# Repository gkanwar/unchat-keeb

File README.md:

# Overview
This repository contains the design materials, firmware, and related docs for
two iterations (2023 and 2024) of the **"Unchat" keyboard**.  Highlights of this
design include:

 * An **ergonomic, split form keyboard** with 40 keys (2024) or 42 keys (2023)
 * **Custom Rust firmware** supporting QMK JSON keymaps using a limited feature set
 * **Hardware chatter mitigation** through Hall Effect magnetic switches (2024)
   or hardware debouncing circuitry (2023)
 * **Diode-free** using a 6-bit bus (2023) or 4-bit analog muxes (2024)

Here are some photos.

The **Unchat-42 (2023)**:

Designing the PCB in Kicad and the results:

The **Unchat-40 (2024)** (assembly still WIP):

## Why design a custom keyboard?
This project was motivated in small part by wanting to solve frustrating key
chatter on my main keyboard and in larger part as a way to kill free time during
holiday seasons. It was an awesome way to learn several new skills. I recommend
this sort of project if any of these interest you as well:

 * PCB design in Kicad
 * Mechanical design in OpenSCAD
 * Electronic assembly and debugging
 * Embedded Rust

## Free to use and share
Designs and code in this repository are covered by the CC0 license, allowing
anyone to freely copy, modify, or distribute these materials. Attribution not
required.

That said, there are some known issues with the original designs. These are
documented below, along with my workarounds. In some cases, these issues are
corrected in the latest design files, but corrections have not been tested. You
may discover other issues that I have not personally encountered. **Use at your
own risk!**

# Unchat-40 (2024)

## Design overview
Summary of design features:

 * Two **reversible PCBs** connected via RJ45
 * Controlled by an **Adafruit QT Py RP2040**
 * **Hall-effect** switches queried via **analog muxes**
 * Acrylic and/or aluminum plate and frame

The 2023 design was fairly successful at reducing key chatter without software
debouncing, but I still experienced occasional chatter (see below).
Unfortunately, this was on timescales far above the filtering provided by the
hardware debouncing, likely due to corrosion and mechanical deformation in the
switches due to my terrible assembly process.

With this new 2024 design, I entirely circumvented using electrical contacts by
moving to a Hall Effect magnetic switch design. This is also used in some
"gaming-friendly" keyboards because it allows very rapid triggering, but from
the perspective of this design the main advantage is that we can apply
**hysteresis** to completely eliminate chatter. The cheap DRV5055 sensor
fit the design perfectly. Unfortunately, magnetic switches are still fairly
rare and a bit more pricey, but the overall cost was still manageable.

## Electronic design

## Mechanical design

## Cost breakdown

# Unchat-42 (2023)

More design info and post-mortem coming soon!

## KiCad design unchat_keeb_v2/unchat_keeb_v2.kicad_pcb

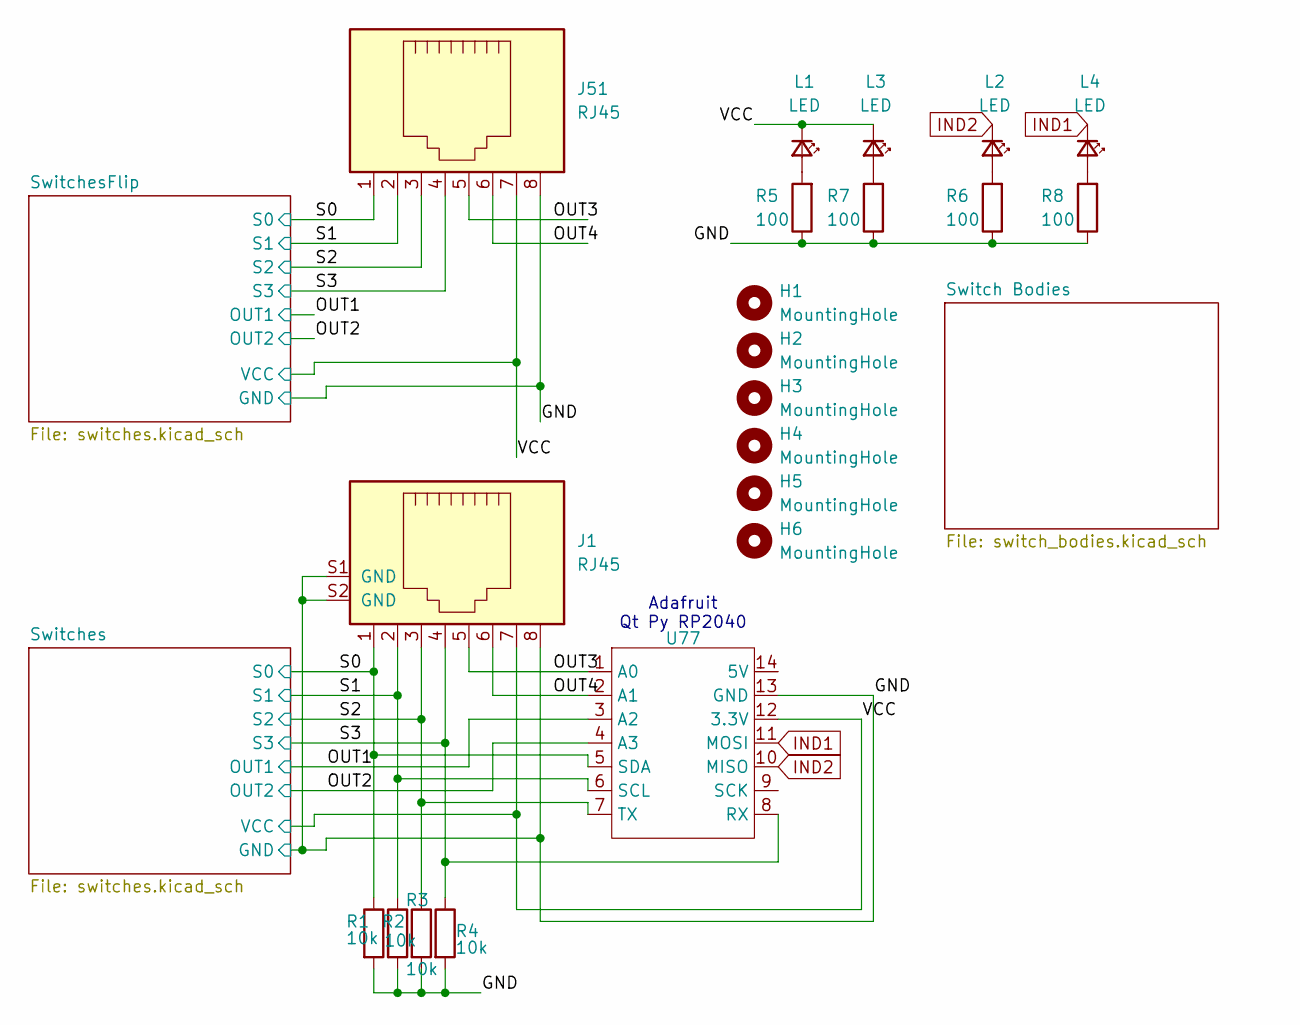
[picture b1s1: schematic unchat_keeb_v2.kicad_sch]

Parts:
H1, H2, H3, H4, H5, H6: MountingHole; MountingHole_2.2mm_M2
J1: RJ45; TE_2041126-1_RJ45
J51: RJ45; TE_2041126-1_RJ45_Back
L1, L2, L3, L4: LED; LED_0603_1608Metric
R1, R2, R3, R4: 10k; R_0805_2012Metric_Pad1.20x1.40mm_HandSolder
R5, R6, R7, R8: 100; R_0805_2012Metric
U77: Adafruit_QT_Py_SMD

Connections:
/GND: J1.8, J1.S1 (GND), J1.S2 (GND), J51.8, R1.2, R2.2, R3.2, R4.2, R5.1, R6.1, R7.1, R8.1, U77.13 (GND); also elsewhere on the board
/OUT1: U77.3 (A2); also elsewhere on the board
/OUT2: U77.4 (A3); also elsewhere on the board
/OUT3: J1.5, J51.5, U77.1 (A0)
/OUT4: J1.6, J51.6, U77.2 (A1)
/S0: J1.1, J51.1, R1.1, U77.5 (SDA); also elsewhere on the board
/S1: J1.2, J51.2, R2.1, U77.6 (SCL); also elsewhere on the board
/S2: J1.3, J51.3, R3.1, U77.7 (TX); also elsewhere on the board
/S3: J1.4, J51.4, R4.1, U77.8 (RX); also elsewhere on the board
/VCC: J1.7, J51.7, L1.1 (K), L3.1 (K), U77.12 (3.3V); also elsewhere on the board
IND1: L4.1 (K), U77.11 (MOSI)
IND2: L2.1 (K), U77.10 (MISO)
unnamed: L1.2 (A), R5.2
unnamed: L2.2 (A), R6.2
unnamed: L3.2 (A), R7.2
unnamed: L4.2 (A), R8.2

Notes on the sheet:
Adafruit Qt Py RP2040

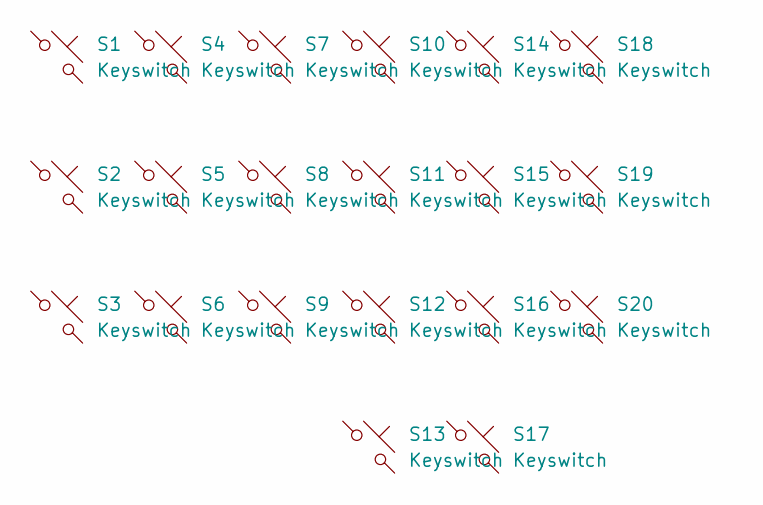
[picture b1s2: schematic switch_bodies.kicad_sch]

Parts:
S1, S2, S3, S4, S5, S6, S7, S8, S9, S10, S11, S12, S13, S14, S15, S16, S17, S18, S19, S20: Keyswitch; MX_HallEffect_Reversible_1.00u

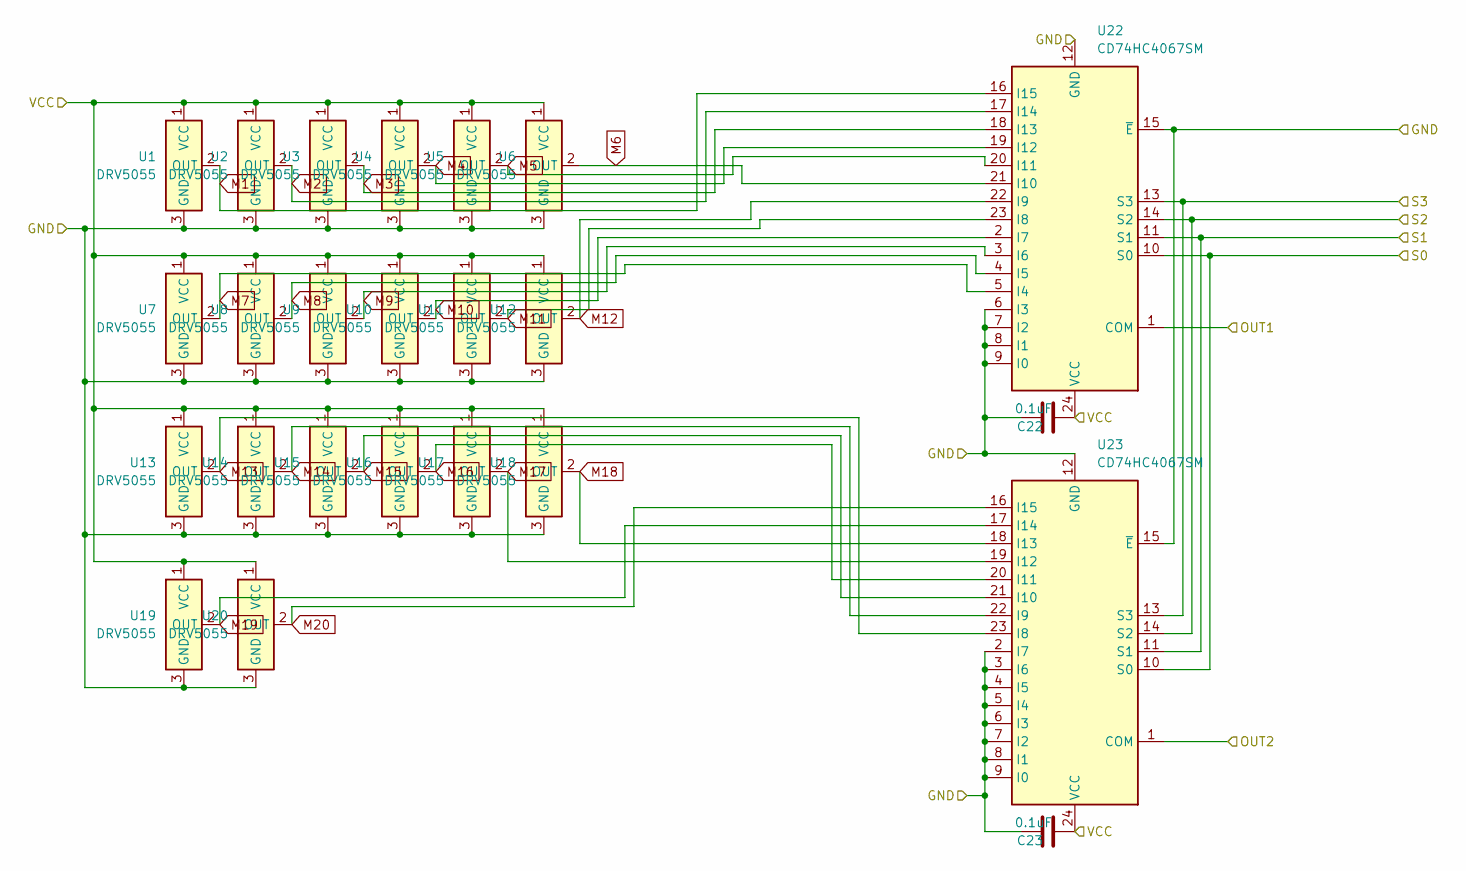
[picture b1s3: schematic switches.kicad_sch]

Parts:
C22, C23: 0.1uF; C_0805_2012Metric_Pad1.18x1.45mm_HandSolder
U1, U2, U3, U4, U5, U6, U7, U8, U9, U10, U11, U12, U13, U14, U15, U16, U17, U18, U19, U20: DRV5055; SOT-23
U22, U23: CD74HC4067SM; SSOP-24_5.3x8.2mm_P0.65mm

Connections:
/GND: C22.1, C23.1, U1.3 (GND), U2.3 (GND), U3.3 (GND), U4.3 (GND), U5.3 (GND), U6.3 (GND), U7.3 (GND), U8.3 (GND), U9.3 (GND), U10.3 (GND), U11.3 (GND), U12.3 (GND), U13.3 (GND), U14.3 (GND), U15.3 (GND), U16.3 (GND), U17.3 (GND), U18.3 (GND), U19.3 (GND), U20.3 (GND), U22.6 (I3), U22.7 (I2), U22.8 (I1), U22.9 (I0), U22.12 (GND), U22.15 (~E), U23.2 (I7), U23.3 (I6), U23.4 (I5), U23.5 (I4), U23.6 (I3), U23.7 (I2), U23.8 (I1), U23.9 (I0), U23.12 (GND), U23.15 (~E); also elsewhere on the board
/OUT1: U22.1 (COM); also elsewhere on the board
/OUT2: U23.1 (COM); also elsewhere on the board
/S0: U22.10 (S0), U23.10 (S0); also elsewhere on the board
/S1: U22.11 (S1), U23.11 (S1); also elsewhere on the board
/S2: U22.14 (S2), U23.14 (S2); also elsewhere on the board
/S3: U22.13 (S3), U23.13 (S3); also elsewhere on the board
/VCC: C22.2, C23.2, U1.1 (VCC), U2.1 (VCC), U3.1 (VCC), U4.1 (VCC), U5.1 (VCC), U6.1 (VCC), U7.1 (VCC), U8.1 (VCC), U9.1 (VCC), U10.1 (VCC), U11.1 (VCC), U12.1 (VCC), U13.1 (VCC), U14.1 (VCC), U15.1 (VCC), U16.1 (VCC), U17.1 (VCC), U18.1 (VCC), U19.1 (VCC), U20.1 (VCC), U22.24 (VCC), U23.24 (VCC); also elsewhere on the board
M1: U1.2 (OUT), U22.16 (I15); also elsewhere on the board
M2: U2.2 (OUT), U22.17 (I14); also elsewhere on the board
M3: U3.2 (OUT), U22.18 (I13); also elsewhere on the board
M4: U4.2 (OUT), U22.19 (I12); also elsewhere on the board
M5: U5.2 (OUT), U22.20 (I11); also elsewhere on the board
M6: U6.2 (OUT), U22.21 (I10); also elsewhere on the board
M7: U7.2 (OUT), U22.5 (I4); also elsewhere on the board
M8: U8.2 (OUT), U22.4 (I5); also elsewhere on the board
M9: U9.2 (OUT), U22.3 (I6); also elsewhere on the board
M10: U10.2 (OUT), U22.2 (I7); also elsewhere on the board
M11: U11.2 (OUT), U22.23 (I8); also elsewhere on the board
M12: U12.2 (OUT), U22.22 (I9); also elsewhere on the board
M13: U13.2 (OUT), U23.23 (I8); also elsewhere on the board
M14: U14.2 (OUT), U23.22 (I9); also elsewhere on the board
M15: U15.2 (OUT), U23.21 (I10); also elsewhere on the board
M16: U16.2 (OUT), U23.20 (I11); also elsewhere on the board
M17: U17.2 (OUT), U23.19 (I12); also elsewhere on the board
M18: U18.2 (OUT), U23.18 (I13); also elsewhere on the board
M19: U19.2 (OUT), U23.17 (I14); also elsewhere on the board
M20: U20.2 (OUT), U23.16 (I15); also elsewhere on the board

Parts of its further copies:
C72, C73: 0.1uF; C_0805_2012Metric_Pad1.18x1.45mm_HandSolder
U51, U52, U53, U54, U55, U56, U57, U58, U59, U60, U61, U62, U63, U64, U65, U66, U67, U68, U69, U70: DRV5055; SOT-23
U72, U73: CD74HC4067SM; SSOP-24_5.3x8.2mm_P0.65mm

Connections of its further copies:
/GND: C72.1, C73.1, U51.3 (GND), U52.3 (GND), U53.3 (GND), U54.3 (GND), U55.3 (GND), U56.3 (GND), U57.3 (GND), U58.3 (GND), U59.3 (GND), U60.3 (GND), U61.3 (GND), U62.3 (GND), U63.3 (GND), U64.3 (GND), U65.3 (GND), U66.3 (GND), U67.3 (GND), U68.3 (GND), U69.3 (GND), U70.3 (GND), U72.6 (I3), U72.7 (I2), U72.8 (I1), U72.9 (I0), U72.12 (GND), U72.15 (~E), U73.2 (I7), U73.3 (I6), U73.4 (I5), U73.5 (I4), U73.6 (I3), U73.7 (I2), U73.8 (I1), U73.9 (I0), U73.12 (GND), U73.15 (~E); also elsewhere on the board
/OUT1: U72.1 (COM); also elsewhere on the board
/OUT2: U73.1 (COM); also elsewhere on the board
/S0: U72.10 (S0), U73.10 (S0); also elsewhere on the board
/S1: U72.11 (S1), U73.11 (S1); also elsewhere on the board
/S2: U72.14 (S2), U73.14 (S2); also elsewhere on the board
/S3: U72.13 (S3), U73.13 (S3); also elsewhere on the board
/VCC: C72.2, C73.2, U51.1 (VCC), U52.1 (VCC), U53.1 (VCC), U54.1 (VCC), U55.1 (VCC), U56.1 (VCC), U57.1 (VCC), U58.1 (VCC), U59.1 (VCC), U60.1 (VCC), U61.1 (VCC), U62.1 (VCC), U63.1 (VCC), U64.1 (VCC), U65.1 (VCC), U66.1 (VCC), U67.1 (VCC), U68.1 (VCC), U69.1 (VCC), U70.1 (VCC), U72.24 (VCC), U73.24 (VCC); also elsewhere on the board
M1: U51.2 (OUT), U72.16 (I15); also elsewhere on the board
M2: U52.2 (OUT), U72.17 (I14); also elsewhere on the board
M3: U53.2 (OUT), U72.18 (I13); also elsewhere on the board
M4: U54.2 (OUT), U72.19 (I12); also elsewhere on the board
M5: U55.2 (OUT), U72.20 (I11); also elsewhere on the board
M6: U56.2 (OUT), U72.21 (I10); also elsewhere on the board
M7: U57.2 (OUT), U72.5 (I4); also elsewhere on the board
M8: U58.2 (OUT), U72.4 (I5); also elsewhere on the board
M9: U59.2 (OUT), U72.3 (I6); also elsewhere on the board
M10: U60.2 (OUT), U72.2 (I7); also elsewhere on the board
M11: U61.2 (OUT), U72.23 (I8); also elsewhere on the board
M12: U62.2 (OUT), U72.22 (I9); also elsewhere on the board
M13: U63.2 (OUT), U73.23 (I8); also elsewhere on the board
M14: U64.2 (OUT), U73.22 (I9); also elsewhere on the board
M15: U65.2 (OUT), U73.21 (I10); also elsewhere on the board
M16: U66.2 (OUT), U73.20 (I11); also elsewhere on the board
M17: U67.2 (OUT), U73.19 (I12); also elsewhere on the board
M18: U68.2 (OUT), U73.18 (I13); also elsewhere on the board
M19: U69.2 (OUT), U73.17 (I14); also elsewhere on the board
M20: U70.2 (OUT), U73.16 (I15); also elsewhere on the board

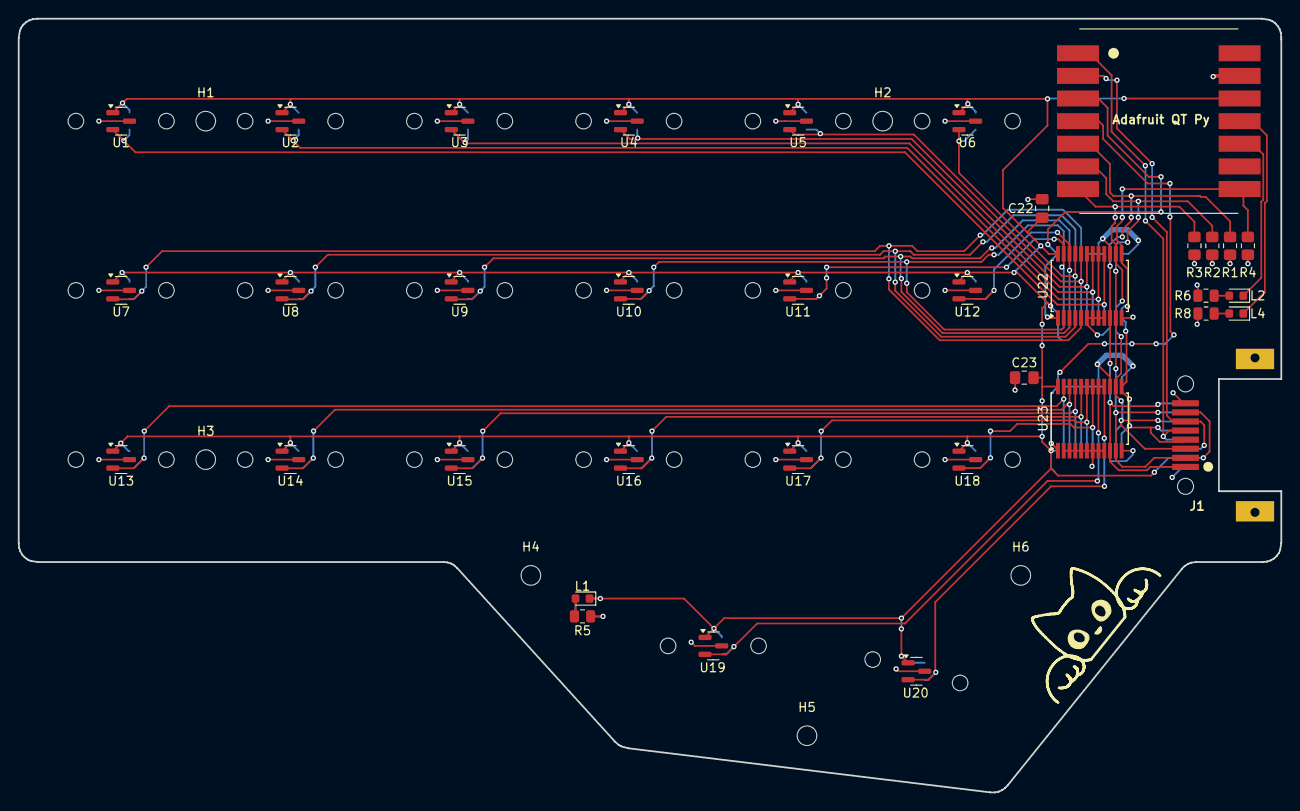
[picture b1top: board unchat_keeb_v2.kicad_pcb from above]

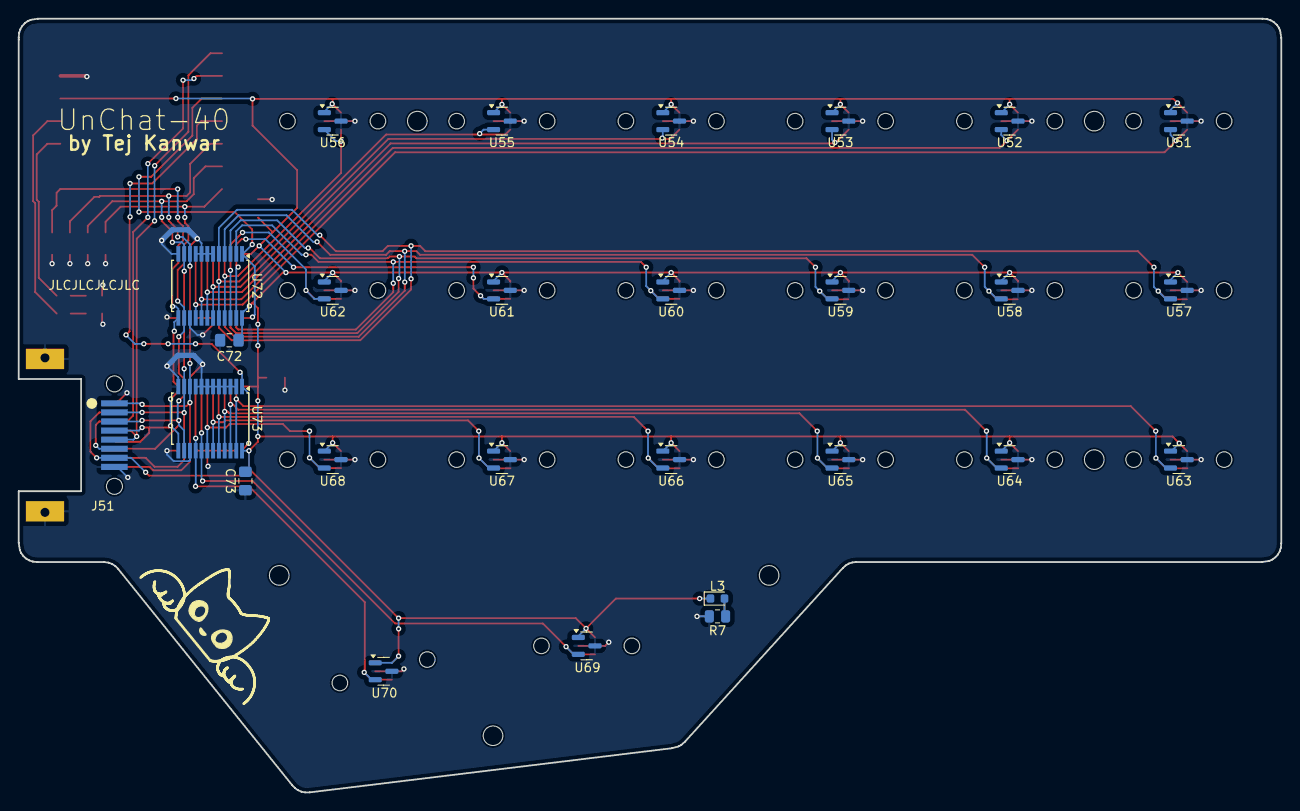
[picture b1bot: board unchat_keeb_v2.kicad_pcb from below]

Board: 2 copper layers, 141.8 x 86.9 mm, 89 parts (27 on the bottom side), 36 nets.

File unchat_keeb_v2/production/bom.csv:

Designator,Footprint,Quantity,Value,LCSC Part #
"C22, C23, C72, C73",0805,4,0.1uF,
J1,TE_2041126-1_RJ45,1,RJ45,
J51,TE_2041126-1_RJ45_Back,1,RJ45,
"L1, L2, L3, L4",0603,4,LED,
"R1, R2, R3, R4",0805,4,10k,
"R5, R6, R7, R8",0805,4,100,
"S1, S10, S11, S12, S13, S14, S15, S16, S17, S18, S19, S2, S20, S3, S4, S5, S6, S7, S8, S9",MX_HallEffect_Reversible_1.00u,20,Keyswitch,
"U1, U10, U11, U12, U13, U14, U15, U16, U17, U18, U19, U2, U20, U3, U4, U5, U51, U52, U53, U54, U55, U56, U57, U58, U59, U6, U60, U61, U62, U63, U64, U65, U66, U67, U68, U69, U7, U70, U8, U9",SOT-23,40,DRV5055,
"U22, U23, U72, U73",SSOP-24_5.3x8.2mm_P0.65mm,4,CD74HC4067SM,
U77,Adafruit_QT_Py_SMD,1,~,

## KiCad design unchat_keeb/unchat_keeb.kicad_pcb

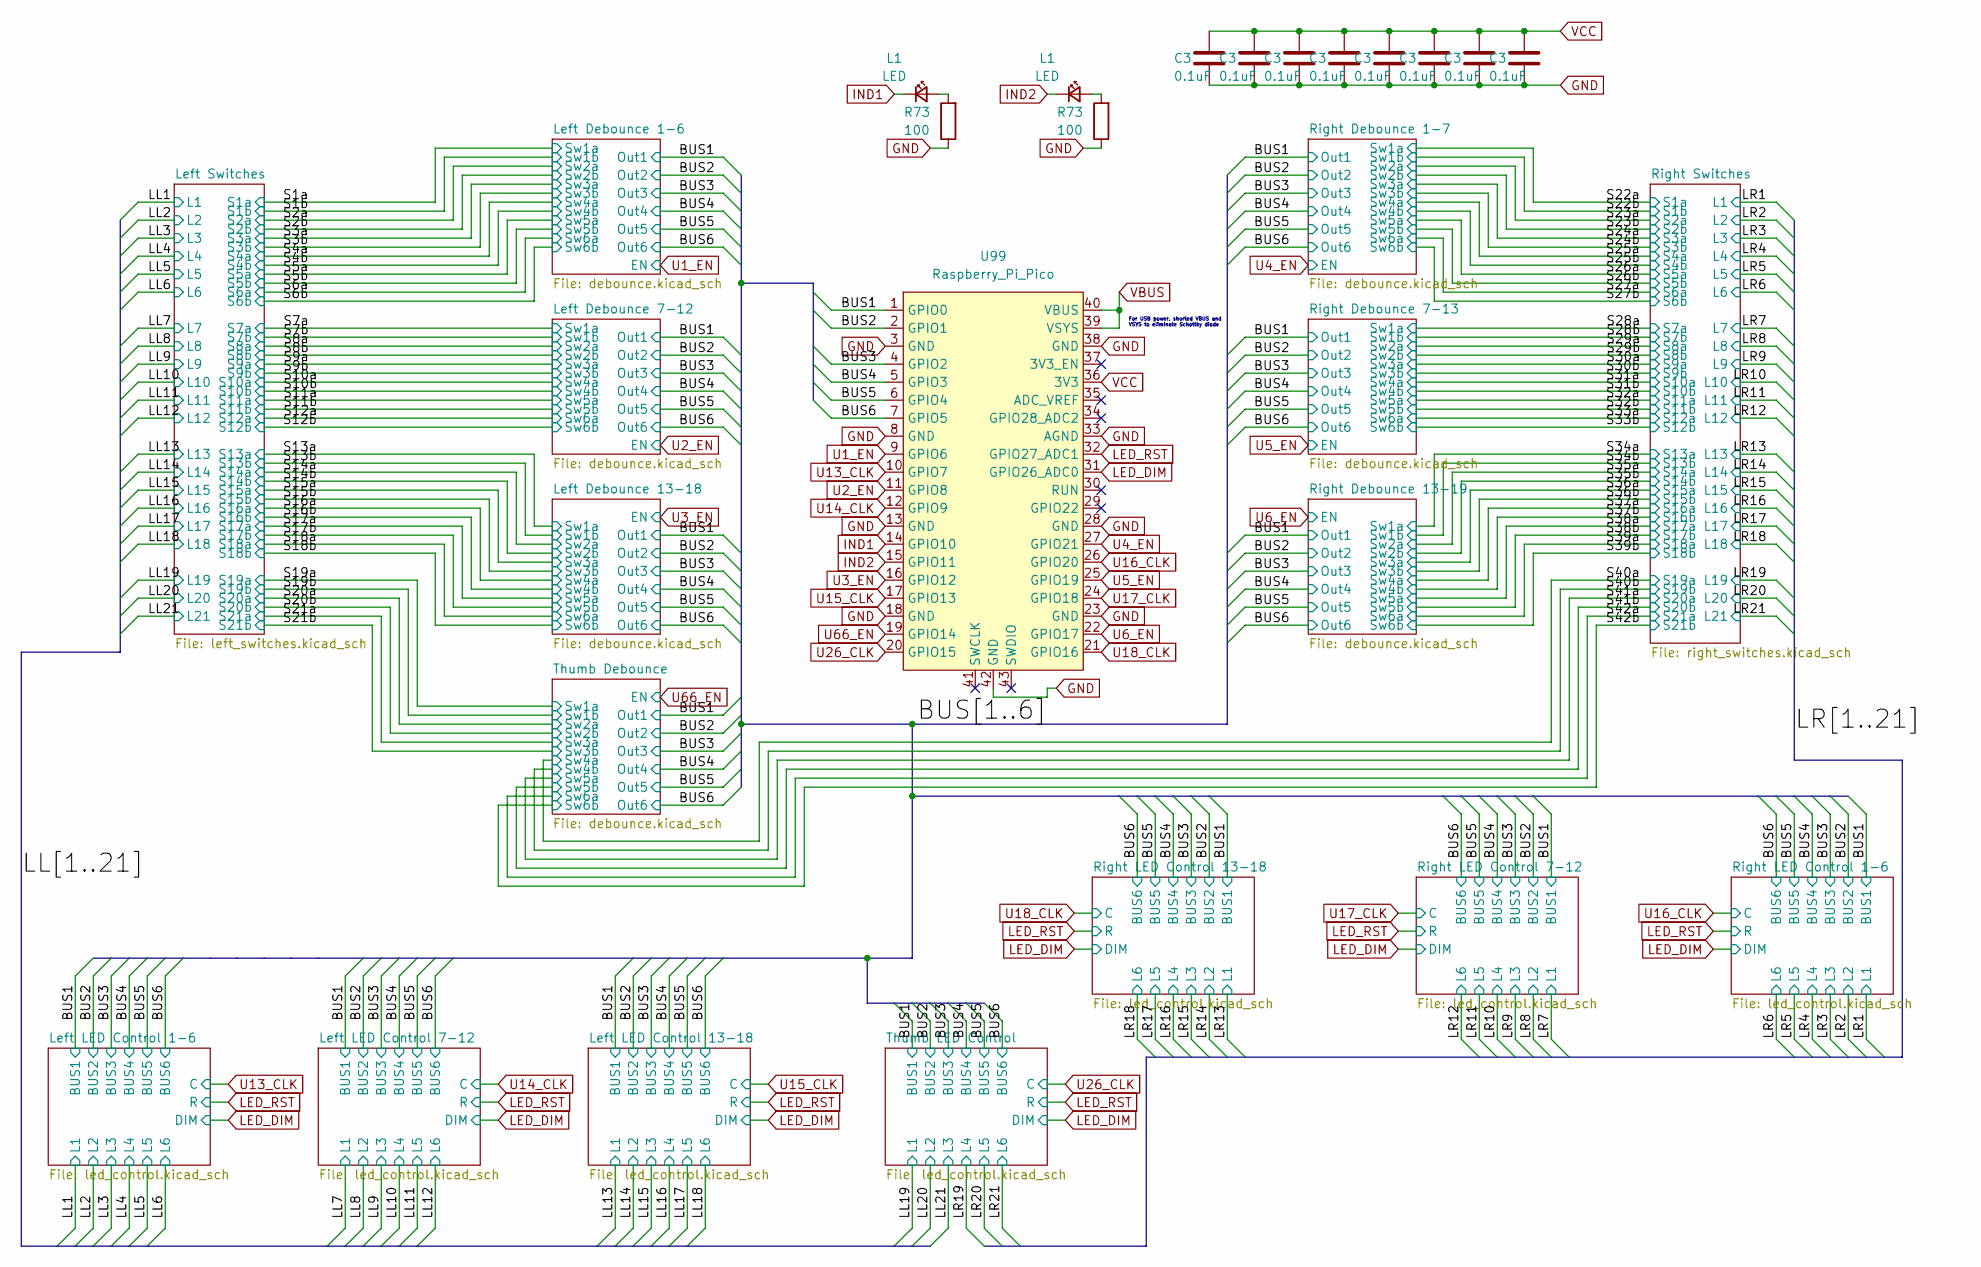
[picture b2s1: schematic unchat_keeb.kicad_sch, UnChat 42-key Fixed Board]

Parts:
C3: 0.1uF; C_0805_2012Metric
L1: LED; LED_0603_1608Metric
R73: 100; R_0805_2012Metric
U99: Raspberry_Pi_Pico; Raspberry_Pi_Pico_SMD

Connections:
/BUS1: U99.1 (GPIO0); also elsewhere on the board
/BUS2: U99.2 (GPIO1); also elsewhere on the board
/BUS3: U99.4 (GPIO2); also elsewhere on the board
/BUS4: U99.5 (GPIO3); also elsewhere on the board
/BUS5: U99.6 (GPIO4); also elsewhere on the board
/BUS6: U99.7 (GPIO5); also elsewhere on the board
GND: C3.2, R73.1, U99.3 (GND), U99.8 (GND), U99.13 (GND), U99.18 (GND), U99.23 (GND), U99.28 (GND), U99.33 (AGND), U99.38 (GND), U99.42 (GND); also elsewhere on the board
LED_DIM: U99.31 (GPIO26_ADC0); also elsewhere on the board
LED_RST: U99.32 (GPIO27_ADC1); also elsewhere on the board
unnamed: L1.2 (A), R73.2
U1_EN: U99.9 (GPIO6); also elsewhere on the board
U2_EN: U99.11 (GPIO8); also elsewhere on the board
U3_EN: U99.16 (GPIO12); also elsewhere on the board
U4_EN: U99.27 (GPIO21); also elsewhere on the board
U5_EN: U99.25 (GPIO19); also elsewhere on the board
U6_EN: U99.22 (GPIO17); also elsewhere on the board
U13_CLK: U99.10 (GPIO7); also elsewhere on the board
U14_CLK: U99.12 (GPIO9); also elsewhere on the board
U15_CLK: U99.17 (GPIO13); also elsewhere on the board
U16_CLK: U99.26 (GPIO20); also elsewhere on the board
U17_CLK: U99.24 (GPIO18); also elsewhere on the board
U18_CLK: U99.21 (GPIO16); also elsewhere on the board
U26_CLK: U99.20 (GPIO15); also elsewhere on the board
U66_EN: U99.19 (GPIO14); also elsewhere on the board
VBUS: U99.39 (VSYS), U99.40 (VBUS)

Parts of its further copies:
C9, C15, C21, C27, C33, C39, C43, C44, C45, C46, C47, C48, C49, C50: 0.1uF; C_0805_2012Metric
L37, L38: LED; LED_0603_1608Metric
R109, R110: 100; R_0805_2012Metric

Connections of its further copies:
/Left Debounce 7-12/Db3: C9.1; also elsewhere on the board
/Left Debounce 13-18/Db3: C15.1; also elsewhere on the board
/Right Debounce 1-7/Db3: C21.1; also elsewhere on the board
/Right Debounce 7-13/Db3: C27.1; also elsewhere on the board
/Right Debounce 13-19/Db3: C33.1; also elsewhere on the board
/Thumb Debounce/Db3: C39.1; also elsewhere on the board
GND: C9.2, C15.2, C21.2, C27.2, C33.2, C39.2, C43.2, C44.2, C45.2, C46.2, C47.2, C48.2, C49.2, C50.2, R109.1, R110.1; also elsewhere on the board
unnamed: L37.2 (A), R109.2
unnamed: L38.2 (A), R110.2

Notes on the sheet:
For USB power, shorted VBUS and VSYS to eliminate Schottky diode

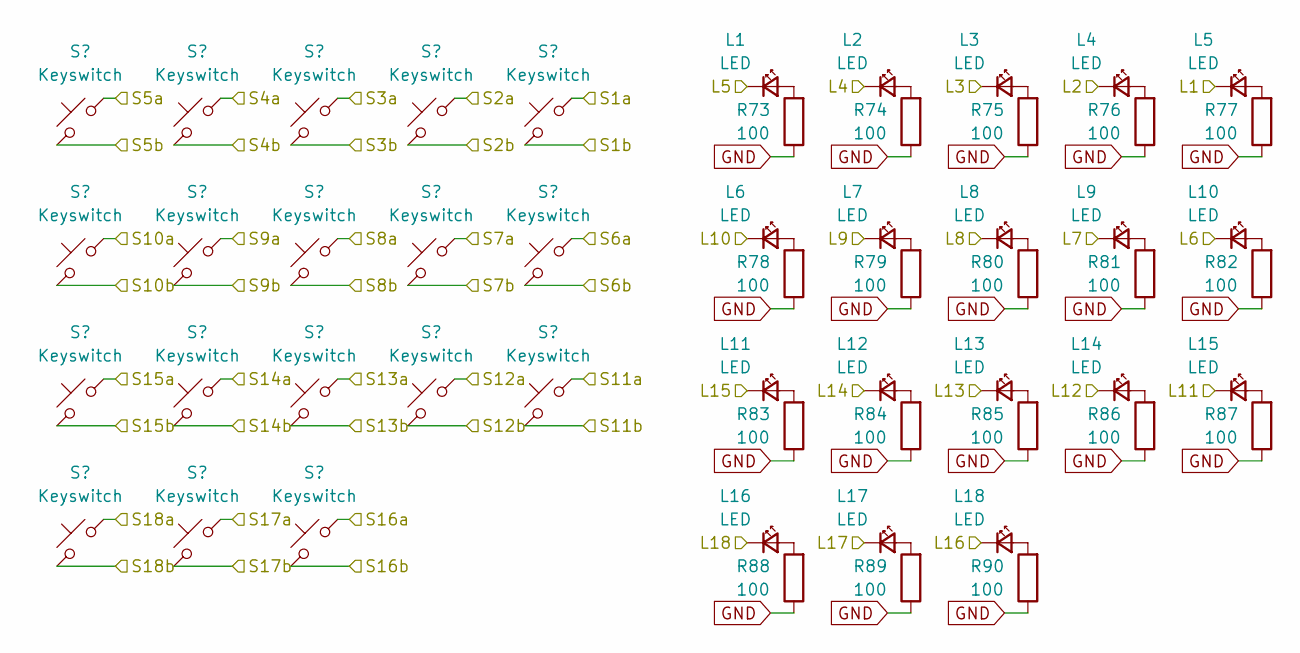
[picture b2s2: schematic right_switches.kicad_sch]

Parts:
L1, L2, L3, L4, L5, L6, L7, L8, L9, L10, L11, L12, L13, L14, L15, L16, L17, L18: LED; LED_0603_1608Metric
R73, R74, R75, R76, R77, R78, R79, R80, R81, R82, R83, R84, R85, R86, R87, R88, R89, R90: 100; R_0805_2012Metric
S1, S2, S3, S4, S5, S6, S7, S8, S9, S10, S11, S12, S13, S14, S15, S16: Keyswitch; Choc_V1_LED_1.00u
S17, S18: Keyswitch; Choc_V1_LED_1.50u_90deg

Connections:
/LL2: L2.1 (K); also elsewhere on the board
/LL3: L3.1 (K); also elsewhere on the board
/LL4: L4.1 (K); also elsewhere on the board
/LL5: L5.1 (K); also elsewhere on the board
/LL6: L6.1 (K); also elsewhere on the board
/LL7: L7.1 (K); also elsewhere on the board
/LL8: L8.1 (K); also elsewhere on the board
/LL9: L9.1 (K); also elsewhere on the board
/LL10: L10.1 (K); also elsewhere on the board
/LL11: L11.1 (K); also elsewhere on the board
/LL12: L12.1 (K); also elsewhere on the board
/LL13: L13.1 (K); also elsewhere on the board
/LL14: L14.1 (K); also elsewhere on the board
/LL15: L15.1 (K); also elsewhere on the board
/LL16: L16.1 (K); also elsewhere on the board
/LL17: L17.1 (K); also elsewhere on the board
/LL18: L18.1 (K); also elsewhere on the board
/S1a: S1.1; also elsewhere on the board
/S2a: S2.1; also elsewhere on the board
/S3a: S3.1; also elsewhere on the board
/S4a: S4.1; also elsewhere on the board
/S5a: S5.1; also elsewhere on the board
/S6a: S6.1; also elsewhere on the board
/S7a: S7.1; also elsewhere on the board
/S8a: S8.1; also elsewhere on the board
/S9a: S9.1; also elsewhere on the board
/S10a: S10.1; also elsewhere on the board
/S11a: S11.1; also elsewhere on the board
/S12a: S12.1; also elsewhere on the board
/S13a: S13.1; also elsewhere on the board
/S14a: S14.1; also elsewhere on the board
/S15a: S15.1; also elsewhere on the board
/S16a: S16.1; also elsewhere on the board
/S17a: S17.1; also elsewhere on the board
/S18a: S18.1; also elsewhere on the board
GND: R73.1, R74.1, R75.1, R76.1, R77.1, R78.1, R79.1, R80.1, R81.1, R82.1, R83.1, R84.1, R85.1, R86.1, R87.1, R88.1, R89.1, R90.1, S1.2, S2.2, S3.2, S4.2, S5.2, S6.2, S7.2, S8.2, S9.2, S10.2, S11.2, S12.2, S13.2, S14.2, S15.2, S16.2, S17.2, S18.2; also elsewhere on the board
unnamed: L1.2 (A), R73.2
unnamed: L2.2 (A), R74.2
unnamed: L3.2 (A), R75.2
unnamed: L4.2 (A), R76.2
unnamed: L5.2 (A), R77.2
unnamed: L6.2 (A), R78.2
unnamed: L7.2 (A), R79.2
unnamed: L8.2 (A), R80.2
unnamed: L9.2 (A), R81.2
unnamed: L10.2 (A), R82.2
unnamed: L11.2 (A), R83.2
unnamed: L12.2 (A), R84.2
unnamed: L13.2 (A), R85.2
unnamed: L14.2 (A), R86.2
unnamed: L15.2 (A), R87.2
unnamed: L16.2 (A), R88.2
unnamed: L17.2 (A), R89.2
unnamed: L18.2 (A), R90.2

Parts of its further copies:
L22, L23, L24, L25, L26, L27, L28, L29, L30, L31, L32, L33, L34, L35, L36: LED; LED_0603_1608Metric
R91, R92, R93, R94, R95, R96, R97, R98, R99, R100, R101, R102, R103, R104, R105, R106, R107, R108: 100; R_0805_2012Metric
S22, S23, S24, S25, S26, S27, S28, S29, S30, S31, S32, S33, S34: Keyswitch; Choc_V1_LED_1.00u
S35, S36: Keyswitch; Choc_V1_LED_1.50u_90deg

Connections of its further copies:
/LR1: L22.1 (K); also elsewhere on the board
/LR2: L23.1 (K); also elsewhere on the board
/LR3: L24.1 (K); also elsewhere on the board
/LR4: L25.1 (K); also elsewhere on the board
/LR5: L26.1 (K); also elsewhere on the board
/LR6: L27.1 (K); also elsewhere on the board
/LR7: L28.1 (K); also elsewhere on the board
/LR8: L29.1 (K); also elsewhere on the board
/LR9: L30.1 (K); also elsewhere on the board
/LR10: L31.1 (K); also elsewhere on the board
/LR11: L32.1 (K); also elsewhere on the board
/LR12: L33.1 (K); also elsewhere on the board
/LR13: L34.1 (K); also elsewhere on the board
/LR14: L35.1 (K); also elsewhere on the board
/LR15: L36.1 (K); also elsewhere on the board
/S22a: S22.1; also elsewhere on the board
/S23a: S23.1; also elsewhere on the board
/S24a: S24.1; also elsewhere on the board
/S25a: S25.1; also elsewhere on the board
/S26a: S26.1; also elsewhere on the board
/S27a: S27.1; also elsewhere on the board
/S28a: S28.1; also elsewhere on the board
/S29a: S29.1; also elsewhere on the board
/S30a: S30.1; also elsewhere on the board
/S31a: S31.1; also elsewhere on the board
/S32a: S32.1; also elsewhere on the board
/S33a: S33.1; also elsewhere on the board
/S34a: S34.1; also elsewhere on the board
/S35a: S35.1; also elsewhere on the board
/S36a: S36.1; also elsewhere on the board
GND: R91.1, R92.1, R93.1, R94.1, R95.1, R96.1, R97.1, R98.1, R99.1, R100.1, R101.1, R102.1, R103.1, R104.1, R105.1, R106.1, R107.1, R108.1, S22.2, S23.2, S24.2, S25.2, S26.2, S27.2, S28.2, S29.2, S30.2, S31.2, S32.2, S33.2, S34.2, S35.2, S36.2; also elsewhere on the board
unnamed: L22.2 (A), R91.2
unnamed: L23.2 (A), R92.2
unnamed: L24.2 (A), R93.2
unnamed: L25.2 (A), R94.2
unnamed: L26.2 (A), R95.2
unnamed: L27.2 (A), R96.2
unnamed: L28.2 (A), R97.2
unnamed: L29.2 (A), R98.2
unnamed: L30.2 (A), R99.2
unnamed: L31.2 (A), R100.2
unnamed: L32.2 (A), R101.2
unnamed: L33.2 (A), R102.2
unnamed: L34.2 (A), R103.2
unnamed: L35.2 (A), R104.2
unnamed: L36.2 (A), R105.2
unnamed 243: R106.2; also elsewhere on the board
unnamed 244: R107.2; also elsewhere on the board
unnamed 245: R108.2; also elsewhere on the board
